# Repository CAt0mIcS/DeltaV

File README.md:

# Delta V - Delta Robot
This repository is where we develop a Delta Robot as a student project. It is currently in the early stages.
Detailed information on the design can be found in the [architectural report](https://github.com/CAt0mIcS/DeltaV/blob/main/docs/architecture/architecture.pdf).

## Stepper Motor Driver
For learning purposes, one of the three required stepper motor drivers will be designed by us. 
### Active development
* Four-layer PCB
* Feedback loop with inline current sensing and adaptive switching frequency
* FPGA controller with external logic interface

#### H-Bridge Testing Circuit

#### 4-layer PCB

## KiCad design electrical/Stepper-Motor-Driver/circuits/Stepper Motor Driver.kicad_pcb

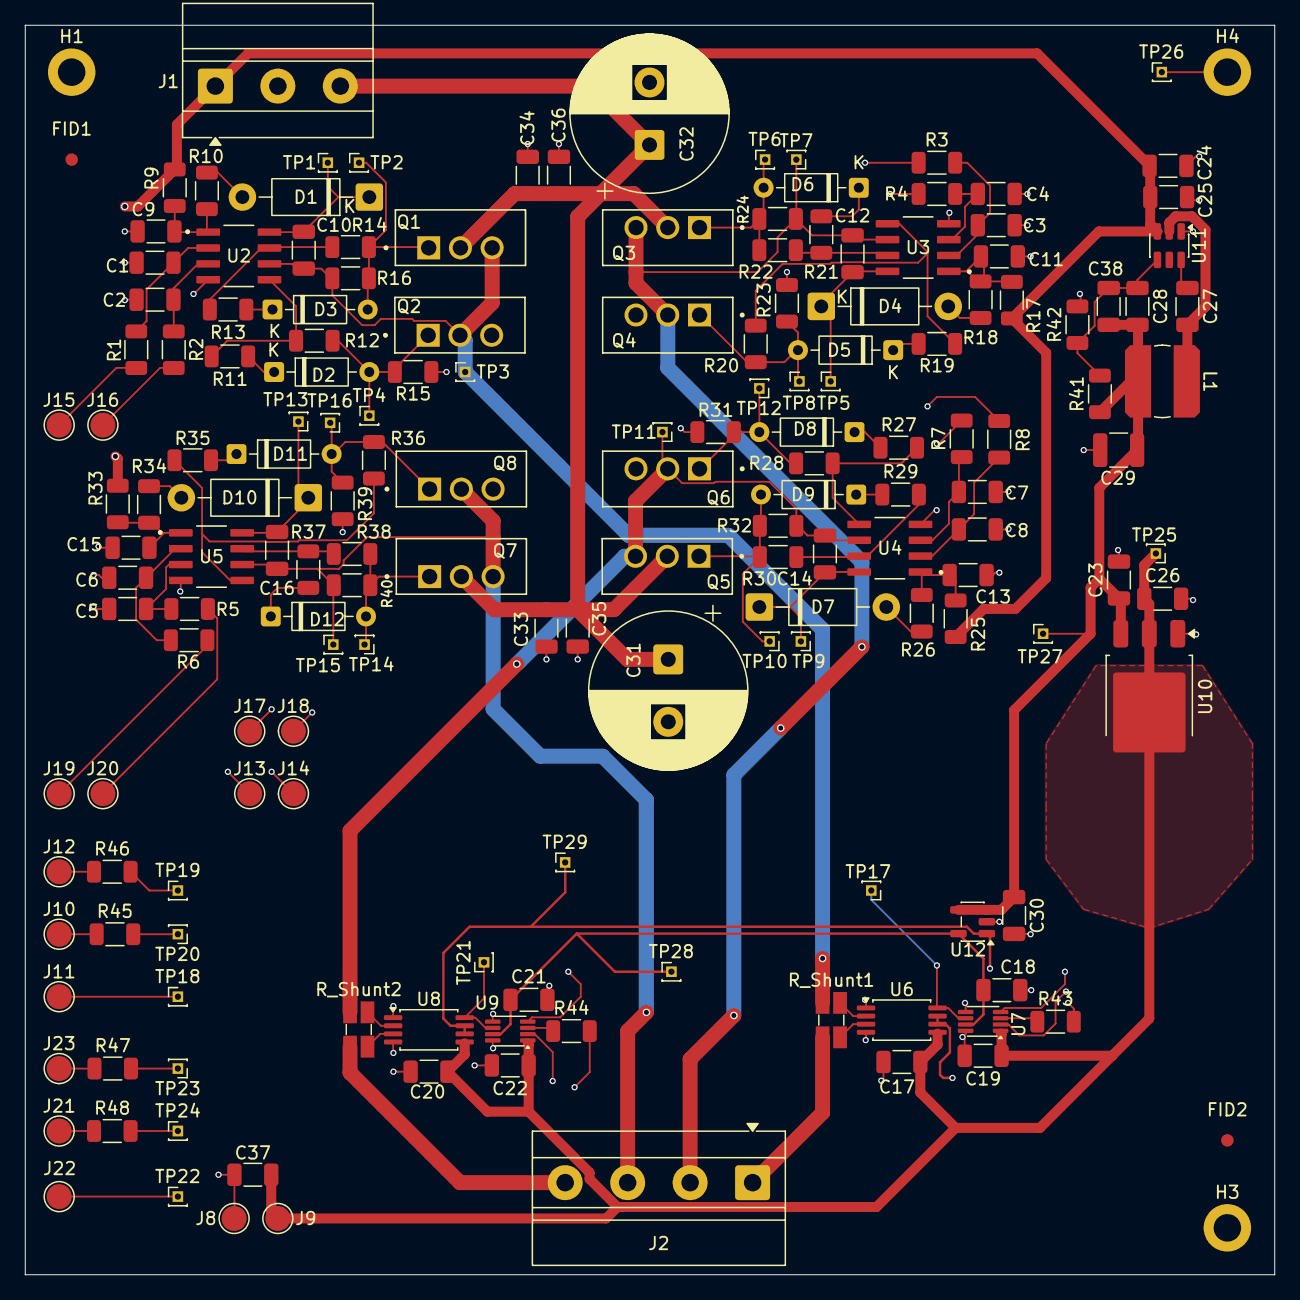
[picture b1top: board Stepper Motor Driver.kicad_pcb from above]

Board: 4 copper layers, 100.0 x 100.0 mm, 172 parts (0 on the bottom side), 86 nets.

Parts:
C1, C2, C3, C4, C5, C6, C7, C8, C28, C38: 33pF; C_1206_3216Metric
C9, C11, C13, C15, C26: 2.2uF; C_1206_3216Metric
C10, C12, C14, C16: 220nF; C_1206_3216Metric
C17, C20, C30: 0.1uF; C_1206_3216Metric
C18, C19, C21, C22, C23, C33, C34: 1uF; C_1206_3216Metric
C24: 4.7uF; C_1206_3216Metric
C25, C27, C35, C36, C37: 100nF; C_1206_3216Metric
C29: 47uF; C_1210_3225Metric
C31, C32: 470uF; CP_Radial_D12.5mm_P5.00mm
D1, D4, D7, D10: 1N5819; D_DO-41_SOD81_P10.16mm_Horizontal
D2, D3, D5, D6, D8, D9, D11, D12: BAT43; D_DO-35_SOD27_P7.62mm_Horizontal
FID1, FID2: Fiducial; Fiducial_1mm_Mask3mm
H1, H3, H4: MountingHole_Pad; MountingHole_2.2mm_M2_DIN965_Pad
J1: Screw_Terminal_01x03; TerminalBlock_MetzConnect_Type011_RT05503HBLC_1x03_P5.00mm_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
J2: Screw_Terminal_01x04; TerminalBlock_MetzConnect_Type011_RT05504HBLC_1x04_P5.00mm_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
J8, J9, J10, J11, J12, J13, J14, J15, J16, J17, J18, J19, J20, J21, J22, J23: Conn_01x01_Socket; TestPoint_Pad_D2.0mm
L1: 4.7uH; L_Bourns_SDR0604
Q1, Q2, Q3, Q4, Q5, Q6, Q7, Q8: IRF530NPBF
R1, R2, R3, R4, R5, R6, R7, R8, R43, R44, R45, R46, R47, R48: 50; R_1206_3216Metric
R9, R12, R14, R17, R20, R22, R25, R28, R30, R33, R36, R38: 10; R_1206_3216Metric
R10, R18, R26, R34: 2.2; R_1206_3216Metric
R11, R13, R19, R21, R27, R29, R35, R37: 5.1; R_1206_3216Metric
R15, R16, R23, R24, R31, R32, R39, R40, R41: 100k; R_1206_3216Metric
R42: 13.7k; R_1206_3216Metric
R_Shunt1, R_Shunt2: LVK12R010CER; R_Shunt_Ohmite_LVK12
TP1, TP2, TP3, TP4, TP5, TP6, TP7, TP8, TP9, TP10, TP11, TP12, TP13, TP14, TP15, TP16, TP17, TP18, TP19, TP20, TP21, TP22, TP23, TP24, TP25, TP26, TP27, TP28, TP29: TestPoint; PinHeader_1x01_P1.00mm_Vertical
U2, U3, U4, U5: UCC27710D
U6, U8: INA240A2PW; TSSOP-8_4.4x3mm_P0.65mm
U7, U9: ADS7042xDCU; VSSOP-8_2.3x2mm_P0.5mm
U10: LM1117-Q1; TO-252-3_TabPin2
U11: TPS54202DDC; SOT-23-6
U12: REF2033; SOT-23-5

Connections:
+1.65V-REF: TP29.1 (1_1), U6.6 (REF2), U6.7 (REF1), U8.6 (REF2), U8.7 (REF1), U12.1 (Vbias)
+3.3V: C17.2, C19.1, C20.2, C22.1, C26.1, C37.1, J9.1 (Pin_1_1), TP25.1 (1_1), U6.5 (V+), U7.1 (DVDD), U8.5 (V+), U9.1 (DVDD), U10.2 (VO)
+3.3V-REF: C18.1, C21.1, TP28.1 (1_1), U7.7 (AVDD), U9.7 (AVDD), U12.5 (Vref)
+5V: C23.1, C28.2, C29.2, C30.1, C38.2, L1.2, R41.1, TP27.1 (1_1), U10.3 (VI), U12.3 (EN), U12.4 (IN)
+12V: C24.2, C25.2, J1.1, R9.2, R17.2, R25.2, R33.2, U11.3 (VIN)
+VMotor: C31.1, C32.1, C33.1, C34.1, C35.1, C36.1, J1.3, Q1.2, Q3.2, Q5.2, Q7.2
/Current Sensor A/IN+: C10.2, Q1.3, Q2.2, R16.2, R_Shunt1.1, TP3.1 (1_1), U2.6 (HS)
/Current Sensor A/IN-: J2.1, R_Shunt1.4
/Current Sensor A/SDO: R43.1, U7.3 (SDO)
/Current Sensor B/IN+: C14.2, Q5.3, Q6.2, R32.2, R_Shunt2.1, TP11.1 (1_1), U4.6 (HS)
/Current Sensor B/IN-: J2.4, R_Shunt2.4
/Current Sensor B/SDO: R44.1, U9.3 (SDO)
/H-Bridge Controller A/BR2: C12.2, J2.2, Q3.3, Q4.2, R24.2, TP7.1 (1_1), U3.6 (HS)
/H-Bridge Controller A/HI1: C1.2, R1.1, U2.2 (HI)
/H-Bridge Controller A/HI2: C3.2, R3.1, U3.2 (HI)
/H-Bridge Controller A/LI1: C2.2, R2.1, U2.3 (LI)
/H-Bridge Controller A/LI2: C4.2, R4.1, U3.3 (LI)
/H-Bridge Controller B/BR2: C16.2, J2.3, Q7.3, Q8.2, R40.2, TP15.1 (1_1), U5.6 (HS)
/H-Bridge Controller B/HI1: C8.2, R8.1, U4.2 (HI)
/H-Bridge Controller B/HI2: C6.2, R6.1, U5.2 (HI)
/H-Bridge Controller B/LI1: C7.2, R7.1, U4.3 (LI)
/H-Bridge Controller B/LI2: C5.2, R5.1, U5.3 (LI)
/HI1A: J15.1 (Pin_1_1), R1.2
/HI1B: J17.1 (Pin_1_1), R8.2
/HI2A: J13.1 (Pin_1_1), R3.2
/HI2B: J19.1 (Pin_1_1), R6.2
/LI1A: J16.1 (Pin_1_1), R2.2
/LI1B: J18.1 (Pin_1_1), R7.2
/LI2A: J14.1 (Pin_1_1), R4.2
/LI2B: J20.1 (Pin_1_1), R5.2
/SCLKA: R45.2, TP20.1 (1_1), U7.2 (SCLK)
/SCLKB: R48.2, TP24.1 (1_1), U9.2 (SCLK)
/SDOA: J11.1 (Pin_1_1), R43.2, TP18.1 (1_1)
/SDOB: J22.1 (Pin_1_1), R44.2, TP22.1 (1_1)
/~CSA: R46.2, TP19.1 (1_1), U7.4 (~CS)
/~CSB: R47.2, TP23.1 (1_1), U9.4 (~CS)
GND: C1.1, C2.1, C3.1, C4.1, C5.1, C6.1, C7.1, C8.1, C9.2, C11.2, C13.2, C15.2, C17.1, C18.2, C19.2, C20.1, C21.2, C22.2, C23.2, C24.1, C25.1, C26.2, C29.1, C30.2, C31.2, C32.2, C33.2, C34.2, C35.2, C36.2, C37.2, H1.1 (1_1), H3.1 (1_1), H4.1 (1_1), J1.2, J8.1 (Pin_1_1), Q2.3, Q4.3, Q6.3, Q8.3, R15.2, R23.2, R31.2, R39.2, R42.2, TP26.1 (1_1), U2.4 (COM), U3.4 (COM), U4.4 (COM), U5.4 (COM), U6.1 (GND), U6.4 (GND), U7.5 (AINM), U7.8 (GND), U8.1 (GND), U8.4 (GND), U9.5 (AINM), U9.8 (GND), U10.1 (GND), U11.1 (GND), U12.2 (GND)
unnamed: D1.2 (A), R10.2
unnamed: C10.1, D1.1 (K), TP1.1 (1_1), U2.8 (HB)
unnamed: D2.2 (A), Q2.1, R12.1, R15.1, TP4.1 (1_1)
unnamed: D2.1 (K), R11.1
unnamed: D3.2 (A), Q1.1, R14.2, R16.1, TP2.1 (1_1)
unnamed: D3.1 (K), R13.1
unnamed: D4.2 (A), R18.2
unnamed: C12.1, D4.1 (K), TP5.1 (1_1), U3.8 (HB)
unnamed: D5.2 (A), Q4.1, R20.1, R23.1, TP8.1 (1_1)
unnamed: D5.1 (K), R19.1
unnamed: D6.2 (A), Q3.1, R22.2, R24.1, TP6.1 (1_1)
unnamed: D6.1 (K), R21.1
unnamed: D7.2 (A), R26.2
unnamed: C14.1, D7.1 (K), TP9.1 (1_1), U4.8 (HB)
unnamed: D8.2 (A), Q6.1, R28.1, R31.1, TP12.1 (1_1)
unnamed: D8.1 (K), R27.1
unnamed: D9.2 (A), Q5.1, R30.2, R32.1, TP10.1 (1_1)
unnamed: D9.1 (K), R29.1
unnamed: D10.2 (A), R34.2
unnamed: C16.1, D10.1 (K), TP13.1 (1_1), U5.8 (HB)
unnamed: D11.2 (A), Q8.1, R36.1, R39.1, TP16.1 (1_1)
unnamed: D11.1 (K), R35.1
unnamed: D12.2 (A), Q7.1, R38.2, R40.1, TP14.1 (1_1)
unnamed: D12.1 (K), R37.1
unnamed: J10.1 (Pin_1_1), R45.1
unnamed: J12.1 (Pin_1_1), R46.1
unnamed: J21.1 (Pin_1_1), R48.1
unnamed: J23.1 (Pin_1_1), R47.1
unnamed: R13.2, R14.1, U2.7 (HO)
unnamed: R11.2, R12.2, U2.5 (LO)
unnamed: C9.1, R9.1, R10.1, U2.1 (VDD)
unnamed: R21.2, R22.1, U3.7 (HO)
unnamed: R19.2, R20.2, U3.5 (LO)
unnamed: C11.1, R17.1, R18.1, U3.1 (VDD)
unnamed: R29.2, R30.1, U4.7 (HO)
unnamed: R27.2, R28.2, U4.5 (LO)
unnamed: C13.1, R25.1, R26.1, U4.1 (VDD)
unnamed: R37.2, R38.1, U5.7 (HO)
unnamed: R35.2, R36.2, U5.5 (LO)
unnamed: C15.1, R33.1, R34.1, U5.1 (VDD)
unnamed: R_Shunt1.2, U6.2 (+)
unnamed: R_Shunt1.3, U6.3 (-)
unnamed: TP17.1 (1_1), U6.8, U7.6 (AINP)
unnamed: R_Shunt2.2, U8.2 (+)
unnamed: R_Shunt2.3, U8.3 (-)
unnamed: TP21.1 (1_1), U8.8, U9.6 (AINP)
unnamed: C27.1, U11.6 (BOOT)
unnamed: C28.1, C38.1, R41.2, R42.1, U11.4 (FB)
unnamed: C27.2, L1.1, U11.2 (SW)
